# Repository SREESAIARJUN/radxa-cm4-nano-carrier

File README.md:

# Radxa CM4 Nano Carrier Board (Revision 5.0)

# Radxa CM4 Nano Carrier Board, Rev 5.0: Engineering Design Document

**Status:** Preliminary. Several specification conflicts must be resolved before layout (see Section 0).

---

## 0. Design Review Findings (Read First)

These issues were found in the input specification. Each one blocks layout or puts first-pass success at risk.

| # | Severity | Issue | Recommendation |
|---|---|---|---|
| R1 | **Blocker** | **Mounting holes at 2.25 mm inset are too close to the edge.** An M2.5 hole needs a Ø2.7 mm drill and a Ø4.5–5.0 mm keep-out pad for the screw head or standoff. A Ø5.0 mm pad at a 2.25 mm inset extends 0.25 mm past the board edge. A 5 mm A/F hex standoff (corner radius ≈ 2.89 mm) overhangs by up to 0.64 mm. This violates the 0.0 mm overhang rule. | Move holes to a ≥3.0 mm inset (pad fully on-board), or use Ø4.0 mm pads with a low-profile M2.5 head. |
| R2 | **Blocker** | **Hole pattern does not match the module.** The CM4 form factor (which Radxa CM-series modules follow) uses a 48.0 × 32.0 mm hole pitch at a 3.5 mm inset (verify against the Radxa mechanical drawing). The specified 50.5 × 35.5 mm pitch will not align with the module's holes. | Adopt the module hole pattern, at least for the shared holes. |
| R3 | **High** | **Connector spacing is unverified.** I cannot confirm that the 15.0 mm centre-to-centre spacing matches the module. A mismatch prevents the module from seating. | Take the connector X/Y origins directly from the Radxa CM4 mechanical DXF. |
| R4 | **High** | *(row truncated by the Rev 5 edit - the complete Rev 4 findings table is preserved in git commit `7eb46b7`)* | See commit `7eb46b7`. |

---

## Revision 9.0 Engineering Changelog

**Task:** Gigabit Ethernet PHY interface: 100-ohm differential routing for TRD0..TRD3 to an ultra-low-profile vertical RJ45.

**Result:** the full 1000BASE-T MDI chain is placed, routed, and verified. It runs from the CM4 module's on-board PHY (DF40 J1 pins 3-12) through discrete magnetics (T1) to a bottom-side vertical RJ45 (J3). The routing passes 4 x 100-ohm pairs on a field-solved stackup, with intra-pair skew of 0.000 mm and zero DRC violations attributable to Rev 9. `tools/ethernet_mdi.py verify` passes **26/26** checks (`artifacts/rev9_mdi_si_report.md`).

### 9.1 Changes implemented

| File | Change |
|---|---|
| `tools/mdi_impedance.py` (new) | The single source of truth for the stackup and the MDI geometry. It contains two independent impedance models: a 2-D finite-difference Laplace field solver (solder mask, finite copper thickness, discrete Gauss-law charge) and the Hammerstad-Jensen / Kirschning-Jansen closed forms. It also has a self-test, a width solver, and a fab-tolerance corner sweep. Run `--check` to exercise all three. |
| `tools/ethernet_mdi.py` (new) | Generator and verifier for the Rev 9 stage. It writes the footprints, places T1/J3/passives, routes all 16 MDI nets plus the centre-tap, Bob Smith, and shield networks, pours the In1/In2 planes, and writes the netclass and DRU rules. The `verify` command checks SI, polarity, and mechanics, runs DRC with mutation tests, and checks ERC and parity. `render` and `schematic` are also provided. |
| `lib/radxa-cm4-nano-carrier.pretty/` | New footprints: `Pulse_H5007NL_SMD-24_P1.27mm`, `Amphenol_RJE231881317T_RJ45_Vertical_SMD`, `C/R_0402_1005Metric`, `C_1206_3216Metric_HV`, `R_1206_3216Metric`. Land patterns are taken from the manufacturer drawings via the LCSC/EasyEDA pad data. |
| `radxa-cm4-nano-carrier.kicad_pcb` | Adds the JLC04161H-7628 stackup (`setup/stackup`), T1, J3, C10-C15, and R10-R14. It adds 4 PHY-side and 4 cable-side 100-ohm pairs, In1/In2 GND planes with an ETH_SHIELD island and a 2.0 mm hi-pot split, and GND/shield stitching. Every Rev 9 item belongs to group `REV9_ETH_MDI`. |
| `radxa-cm4-nano-carrier.kicad_pro` | Adds netclass `ETH_MDI_100R` (W 0.165 / gap 0.125 / via 0.50/0.30) with patterns `Ethernet_Pair*` and `ETH_MDI*`. The netclasses of other stages are preserved. |
| `radxa-cm4-nano-carrier.kicad_dru` | Adds a Rev 9 rule block for track width, diff-pair gap, uncoupled length, length, and via count. It adds `mdi_isolation` (0.30 mm to every other net's tracks, vias, and planes), `mdi_interpair` (0.30 mm), one skew rule (max 0.15 mm) for each of the 8 pair segments, and `eth_shield_split` (2.0 mm on the inner layers). Each rule is shown to be live by a mutation test. |
| `radxa-cm4-nano-carrier.kicad_sch`, `lib/CM4Carrier.kicad_sym` | Adds T1, J3, and C10-C15 / R10-R14 symbols with global labels whose net names are read back from the board. Schematic-to-PCB parity for the Rev 9 parts is clean. |
| `fp-lib-table` | **Bug fix:** the table is now merged rather than overwritten. It registers `CM4Carrier` (used by the schematic hole symbols), which removes the Rev 7 `lib_footprint_issues` DRC errors. |
| `README.md` | **Bug fix:** closed the findings-table row R4, which an earlier edit had truncated mid-sentence. |

### 9.2 Architecture

**Signal chain:** CM4 PHY (on-module) -> J1 DF40 pins 3-12 -> T1 Pulse H5007NL (1000BASE-T, 1CT:1CT, 1500 Vrms, LCSC C6384935) -> J3 Amphenol RJE231881317T (8P8C vertical SMT, shielded, 13.1 mm, LCSC C5384839).

**Placement:** the whole top side lies under the module and is limited to 1.2 mm part height, so T1, J3, and the 1206 HV parts are on **B.Cu**. On the top side there are only eight 0402s (0.55 mm tall) at the T1 centre and cable taps. T1 sits at (34.0, 20.0) with its PHY row facing east and pin 1 at the top. J3 sits at (11.0, 20.0) with its contacts facing T1, and the plug enters from below the carrier.

**Stackup and geometry** (`mdi_impedance.py`): JLC04161H-7628, L1/L4 microstrip over solid L2/L3 GND, 7628 prepreg 0.2104 mm, er 4.4, 10 um LPI mask. The chosen geometry is **W 0.165 mm / S 0.125 mm**, solved with the field solver to **100.03 ohm** (Zodd 50.0, Zcomm 44.2, 5.52 ps/mm).

| Model | Zdiff (ohm) |
|---|---|
| FD field solver, masked (sign-off) | 100.03 |
| FD field solver, bare copper | 104.71 |
| Kirschning-Jansen closed form, bare | 111.06 (its strip-thickness correction under-predicts the side-wall coupling across a 0.125 mm gap with 35 um copper; with thin copper it agrees with the FD solver to within 1.2-1.9 %) |
| Fab corners, one at a time (etch +/-0.02, prepreg +/-10 %, er +/-0.2) | 91.5 - 108.8 (inside +/-10 %) |
| All corners aligned worst case | 88.4 - 112.3, so order JLC impedance control at +/-10 % |

**Channel map and polarity.** On the bottom side both T1 and J3 are mirrored. Their two pad rows then always meet in *reversed* pair order, whatever the rotation. Two degrees of freedom absorb this without any pair crossing:

| CM4 pair | T1 channel (top -> bottom) | P lands on | Cable net | RJ45 pins (+/-) |
|---|---|---|---|---|
| Pair3 (TRD3) | ch1 | TD1- / MX1- | ETH_MDI3 | 7 / 8 |
| Pair1 (TRD1) | ch2 | TD2- / MX2- | ETH_MDI1 | 3 / 6 |
| Pair2 (TRD2) | ch3 | TD3- / MX3- | ETH_MDI2 | 4 / 5 |
| Pair0 (TRD0) | ch4 | TD4- / MX4- | ETH_MDI0 | 1 / 2 |

The four 1CT:1CT channels are identical, and swapping *both* ends of a winding preserves end-to-end polarity. The verifier proves this from the H5007NL dot convention (`MAP-polarity`) and checks the T568 pin map from the copper (`MAP-t568`).

**PHY-side topology:**
- The four pairs leave the 0.4 mm DF40 field. Pair3 and Pair2 come from the outer row through the inter-row gap. Pair1 and Pair0 come from the inner row on F.Cu.
- They run east as nested **F.Cu** bands over the In1 GND plane, then drop south on **B.Cu** over the In2 GND plane in a 43.4-46.8 mm corridor. This corridor is co-planned with the Rev 11 HDMI J4 and the Rev 13 buck. The pairs then turn west into the T1 pads.
- Bands and drops sit over separate solid planes, so they cross freely. **Every pair changes layer exactly once**, and Pair0 uses a compact two-layer via twist.
- GND stitching vias sit beside every layer transition.

**Cable side:** the pairs run almost straight across a 4.1 mm gap, 7.5-11.6 mm per net. Pair C hops to F.Cu with *both* legs, so via counts stay balanced, and passes over pair B's diagonal leg. That leg is the unavoidable T568 3/6 straddle.

**Planes and isolation:**
- In1/In2 are GND everywhere except an **ETH_SHIELD** island (x 0-33, y 11.8-31.5) under the cable side and the jack.
- A **2.0 mm split** runs under the T1 body. This is the 802.3 1500 Vrms functional isolation, enforced by DRU `eth_shield_split`.
- The J3 shield tabs land on the island. R14 (1 Mohm) in parallel with C15 (1 nF / 2 kV, 1206) ties the island to GND and can be tuned at EMC test.
- No MDI segment crosses the split (`REF-domain`), and every MDI segment has copper directly beneath it (`REF-plane`).

**Centre taps:**
- The module PHYs are voltage-mode. Each TCT gets its own **100 nF to GND** (C10-C13, on top under T1). The taps are never shorted together or tied to a supply.
- The cable side uses **Bob Smith** termination: 4 x 75 ohm (R10-R13) to node ETH_BS, then 1 nF / 2 kV (C14) to ETH_SHIELD.

**Pipeline coexistence:**
- Other revisions edit this same board concurrently. The pipeline order is `cm4_mechanical -> ethernet_mdi -> hdmi_tmds -> buck_3v3`.
- `ethernet_mdi.py generate` is **additive and idempotent**. It replaces only its own `REV9_ETH_MDI` group, its footprints, and the Ethernet-net copper and planes, and leaves other stages' groups untouched.
- DRC violations are attributed to Rev 9 by item UUID.

### 9.3 Validation status

| Check | Result |
|---|---|
| Impedance self-test (FD vs H-J / K-J, 8 cases) | PASS, agreement within -1.1 to -1.9 % |
| Nominal Zdiff / fab corners | 100.03 ohm; 91.5-108.8 ohm |
| T568 map, end-to-end polarity, J1 pinout | PASS |
| Intra-pair skew, 8 segments (track + 1.5512 mm per via, KiCad method) | 0.000 mm on all segments (limit 0.15 mm = 0.83 ps) |
| Length per side | max 42.95 mm (limit 50). J1-to-RJ45 totals: 50.9 / 36.5 / 51.5 / 33.6 mm |
| Uncoupled length per net | 3.8-8.8 mm (limit 10). Uncoupled 0.165 mm lines are about 141.7 ohm differential, and the worst case adds -39.6 dB return loss at 100 MHz (limit -30 dB) |
| Pair-to-pair spacing | min 0.495 mm (rule 0.30) |
| Reference planes | 0 voids under MDI copper; 0 split crossings |
| kicad-cli DRC, Rev 9 items | 0 violations, 0 unrouted |
| DRU mutation tests (width, isolation, inter-pair) | 3/3 caught |
| Schematic ERC / PCB parity (Rev 9 refs) | 0 unexpected / 0 parity items |
| CM4 mechanical base (`cm4_mechanical.py verify`) | 32/32 |

**Reproduce:** run `python3 tools/mdi_impedance.py --check`, then `python3 tools/ethernet_mdi.py generate`, `schematic`, `verify`, and `render`.

### 9.4 Open items and assumptions

- **PHY centre-tap mode:** the board assumes voltage-mode drivers (BCM54210PE on RPi CM4, RTL8211F on Radxa CM3). Confirm the Radxa CM4 (RK3576) PHY against its hardware design guide. If it needs a supply on the centre taps, R/C changes at C10-C13 are enough and no reroute is needed.
- **Link/activity LEDs:** J3 has no LEDs, and `Ethernet_nLED1..3` (J1 pins 15/17/19) are left unconnected. Discrete bottom-side LEDs are deferred to a later revision.
- **"Ultra-low-profile":** 13.1 mm is the minimum for a stocked vertical 8P8C with full plug retention. The jack is on the bottom side, so the enclosure needs 13.1 mm of clearance below the carrier.
- **Schematic:** the J1/J2 module connectors are not yet schematic symbols, so the 8 PHY-side `Ethernet_PairN` global labels are expected ERC "dangling" warnings.
- **DF40 pad field:** inside the 0.4 mm-pitch field, MDI stubs keep the netclass's 0.20 mm clearance to J1 pads. The 0.30 mm `mdi_isolation` rule exempts pads by design.

## Revision 11.0 Engineering Changelog

**Task:** Micro HDMI (Type D) connector with HDMI 2.0 100-ohm TMDS differential pairs, length-matched to within 0.15 mm.
**Result:** all 8 TMDS nets are routed and length-matched to **0.0 µm**, measured from the saved copper (each net is 45.1256 mm pad to pad, plus one 1.551 mm via barrel).
**Verification:** `python3 tools/hdmi_tmds.py verify` passes **26/26** checks. Report: `artifacts/rev11_hdmi_tmds_report.md`.

### Changes implemented
- **New stage `tools/hdmi_tmds.py`** (`generate` / `verify` / `solve`). It is the single source of truth for the HDMI0 TMDS breakout and should be edited instead of the copper. `generate` is idempotent: before loading the board it strips its own previous output at the S-expression level. Python deletion through pcbnew is not used because KiCad 8.0.9's SWIG bindings corrupt the board's item lists after `BOARD.Remove()` on tracks.
  Run order: `cm4_mechanical.py generate` → `ethernet_mdi.py generate` → `hdmi_tmds.py generate`. The earlier stages rebuild the board; this one is additive.
- **J4 = XUNPU HDMI-101S Micro-HDMI Type D** (LCSC C720620, 52k in stock).
  - **Footprint:** `lib/radxa-cm4-nano-carrier.pretty/HDMI_Micro-D_XUNPU_HDMI-101S.kicad_mod`. The land pattern is entered numerically from the LCSC/EasyEDA footprint: 19 pads at 0.2 × 0.84 / 0.2 × 1.0 mm in two staggered 0.4 mm-pitch rows, plus 4 oval THT shell slots (Ø0.7 × 1.7 mm).
  - **Placement:** bottom side at (44.0, 36.0). The mouth is 0.25 mm inside the Y=40 edge (zero overhang), and the shell-pad copper is 0.34 mm from the edge. The courtyard clears the H4 standoff keep-out by 0.25 mm. The THT shell legs (X ≥ 40.15) clear the top-side J2 DF40 body (ends at X 36.3).
  - **Pin map:** 3/5 D2, 6/8 D1, 9/11 D0, 12/14 CLK, 1 HPD, 15 CEC, 17 SCL, 18 SDA, 19 `HDMI0_5V`; GND on 4/7/10/13/16 and the shell.
- **Rev 5 envelope was not buildable.** It put uHDMI at X 34.5–41.5, where the shell legs would land inside J2's top-side body. `board_outline.dxf` (via `cm4_mechanical.py`) now carries the real J4 courtyard instead.
- **Impedance:** W 0.165 mm / S 0.125 mm. Solved with the validated 2-D FD solver in `tools/mdi_impedance.py` for the JLC04161H-7628 stackup: Zdiff 100.03 Ω, eeff,odd 2.742, 5.52 ps/mm. The same geometry is used on L1 (over In1 GND) and L4 (over In2 GND).
- **Routing.** Every pair follows the same topology: J4 → north → top lane → west → column (X 37.30 / 38.16) → south → strip lane → west → J2 outer-row pins 170–190.
  - The rear-row pairs (D2→TX2, D0→TX0) run on B.Cu.
  - The front-row pairs (D1→TX1, CLK) cannot pass between the 0.2 mm-gap rear pads. They change layer through a via pair 0.87 mm in front of J4 and run on F.Cu, inside the gap between J2's two pad rows.
  - Every TMDS net has **exactly one via**, so the via barrel cancels in every comparison. Both outer layers are identical microstrips, so physical length equals electrical length.
  - P/N polarity is preserved end to end with no crossovers. TX2's vias sit outboard of the J2 outer row for this reason.
- **Length matching** (solved, then measured back from the copper):
  - *Inter-pair:* chamfered trombones. TX2 gets 3 × 2.45 mm and TX0 3 × 2.58 mm on B.Cu, interleaved between the two strip lanes. TX1 gets 1 × 3.20 mm on its F.Cu riser. Each is found by bisection on the measured length. CLK is naturally the longest and sets the 45.1256 mm target.
  - *Intra-pair:* each route turns a net four 45° left, so P is always the inner trace. It starts 0.89–1.03 mm short (4·d·tan 22.5° = 0.24 mm per 45° turn at a 0.29 mm pitch). This is cancelled by 5–7 single-sided 45° phase bumps on P (h 0.18–0.22 mm, 0.3 mm flat), placed at ≥ 1.05 mm pitch so no contiguous uncoupled stretch exceeds 1 mm.
- **Return path and grounding:**
  - TMDS uses the existing In1/In2 GND planes. A full GND pour is added only on a bare board.
  - Outboard GND vias are placed on J2 pins 186/180/192, plus a GND via 0.73 mm east of the TX2 transition (tied to pin 162) and a plane-stitch via 0.93 mm from the D1/CLK transitions.
  - J4 pins 4 and 16 bond to the GND shell legs.
- **Rules:**
  - `.kicad_pro` gets an `HDMI_TMDS` net class: 0.165 mm width / 0.125 mm gap, 0.50/0.30 mm vias (the project minimums), with exact-name patterns because KiCad patterns are glob-only.
  - `.kicad_dru` gets a fenced block (only this block is replaced on regeneration; other stages' blocks are kept):
    - `hdmi0_tmds_skew_<pair>` at max 0.075 mm. KiCad 8 measures `skew` against the group average, so a two-net group gives |P−N| ≤ 0.15 mm.
    - `hdmi0_tmds_length_window` at L ± 0.075 mm on all 8 nets, for inter-pair matching.
    - Track width 0.160–0.170 mm.
    - Diff-pair gap ≥ 0.115 mm.
    - 0.20 mm TMDS-to-other clearance.
    - One via per net.

### Architecture improvements
- **Co-designed floor plan.** The concurrent Ethernet stage owns an `ETH_SHIELD` island and its 2 mm hi-pot split (no GND for X < 36.5 and 9.8 < Y < 33.5), plus RJ45 J3, T1, and MDI routing down the east side. Two earlier J4 placements I tried (left edge, right edge) collided with successive versions of that plan. The final placement keeps every TMDS segment inside the solid-GND "L" (X > 36.5, or Y > 34.1). The verifier samples 10,827 points along and ±0.28 mm beside every segment and confirms each one lies over *filled* GND. Any future floor-plan change that puts TMDS over the split will fail loudly.
- **The verifier measures the copper, not the model.** Every check reads lengths, gaps, coupled intervals (chained segment by segment), reference-plane fill, return-via distances, pad connectivity and mechanics from the saved board with pcbnew. kicad-cli then runs DRC on the real rules.
- **Mutation tests are baseline-relative.** Each one must create a *new* violation on TMDS copper: lengthening one N trace by 0.20 mm must raise `skew_out_of_range`, and adding a GND track 0.15 mm from a TMDS trace must raise `clearance`. Pre-existing violations from other stages can't satisfy them.
- **Independent review:** a 3-lens adversarial review with per-finding refutation confirmed six findings. Four are fixed: a DRU-block deletion that would have wiped the Rev 13/Rev 9 rules, the wrong skew-rule semantics, unconnected J4 GND pins, and a missing TX2 return via. Two are recorded as open items below.

### Validation status
| Item | Status |
|---|---|
| All 8 TMDS nets: max − min ≤ 0.15 mm (inter- **and** intra-pair) | **PASS**: 0.0 µm (0.000 ps) |
| Coupled gap 0.125 mm on every coupled run; pair-to-pair ≥ 0.40 mm | **PASS**: 0.1250 mm / 0.400 mm |
| Longest contiguous uncoupled stretch ≤ 1.0 mm (5.5 ps ≪ ~50 ps edge) | **PASS**: 0.85–0.94 mm |
| Every TMDS segment over filled GND (outside the 0.75 mm via-transition zones) | **PASS**: 0 off-plane of 10,827 samples |
| GND return within 2.0 mm of every layer change | **PASS**: 0.73–1.72 mm |
| kicad-cli DRC, violations touching TMDS / J4 | **PASS**: 0 |
| DRU mutation tests (skew, clearance) | **PASS**: both caught |
| Insertion length vs HDMI 2.0 (UI 168 ps at 5.94 Gbit/s) | 45.13 mm = 249 ps; 0.15 mm = 0.83 ps = 0.5 % UI |
| Whole-board DRC | **Not clean (other stages):** 162 items, none touching TMDS/J4 (mostly Ethernet-stage clearance) |

**Open items (Rev 12+):**
1. J4 shield pins **7, 10, 13** are not connected yet. There is no via site under the F.Cu risers or between the J4 via pairs. Fixing this needs via-in-pad, or a re-planned D1/CLK escape.
2. **TPD4E05U06 ESD** (required by `specs/carrier_specs.md`) is not placed. It will need flow-through placement next to J4 and a re-solve of the length matching through its pads.
3. **`HDMI0_5V`** (pin 19) has no source yet. It needs a current-limited, back-drive-protected 5 V feed.
4. HPD, CEC and DDC are not routed yet.
5. J4 is not in the schematic yet, so schematic/PCB parity is open.
6. The connector mouth/body outline is approximate. Confirm it against the XUNPU mechanical drawing before release.

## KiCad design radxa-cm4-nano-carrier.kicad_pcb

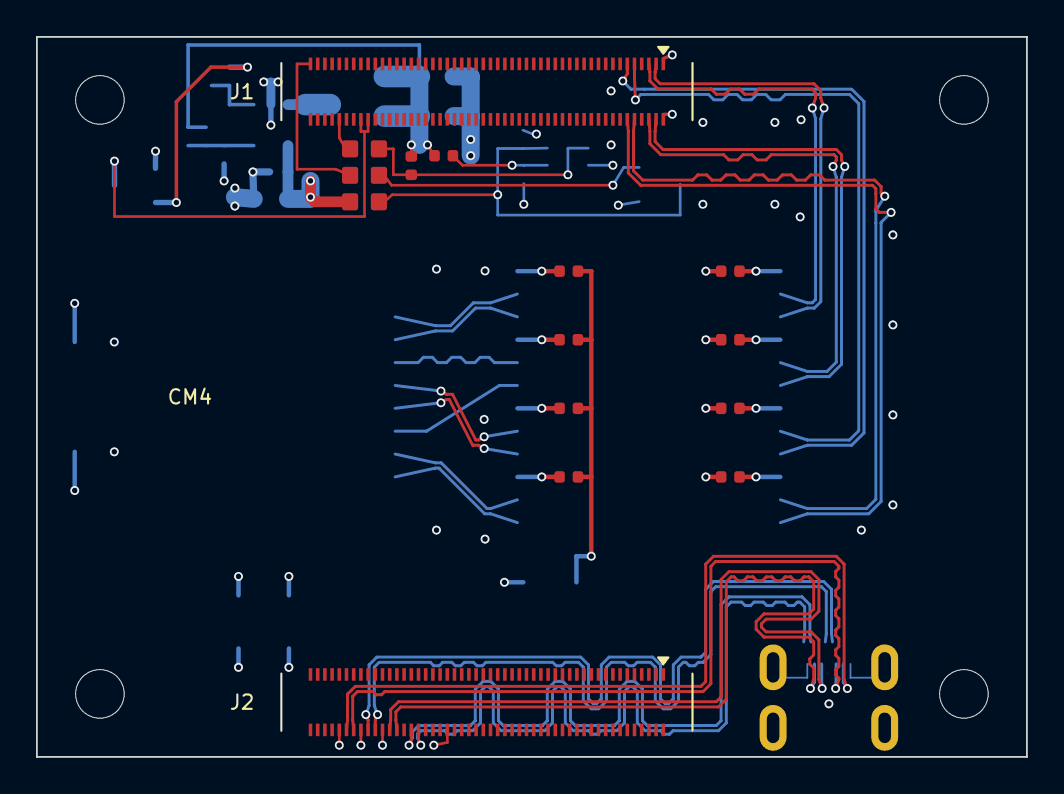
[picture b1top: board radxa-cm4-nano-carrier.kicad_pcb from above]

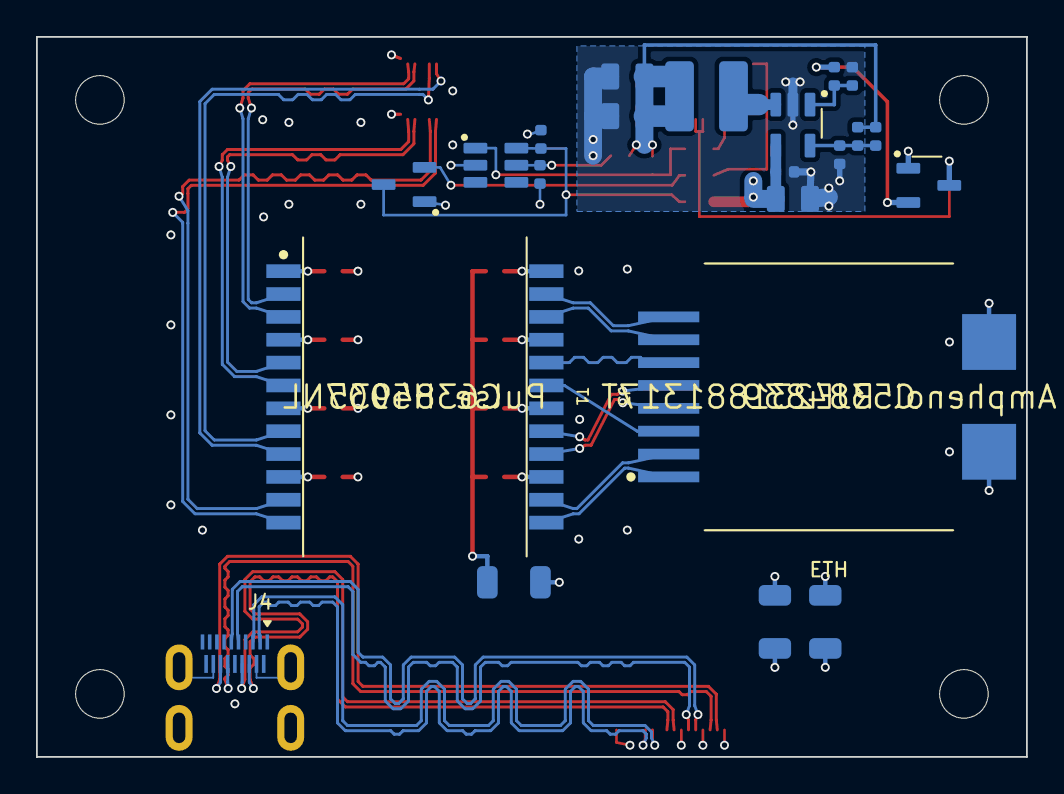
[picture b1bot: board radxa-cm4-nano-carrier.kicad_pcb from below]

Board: 4 copper layers, 55.0 x 40.0 mm, 41 parts (22 on the bottom side), 53 nets.

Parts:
C10, C11, C12, C13, C41, C50: 100nF 16V X7R; C_0402_1005Metric
C14, C15: 1nF 2kV X7R; C_1206_3216Metric_HV
C40, C42, C43: 22uF 25V X5R; C_0805_2012Metric
C44: 47pF 50V C0G; C_0402_1005Metric
H1, H2, H3, H4: M2.5 x 3.0 mm standoff; MountingHole_2.7mm_M2.5_CM4
J1, J2: DF40HC(3.0)-100DS-0.4V(51); Hirose_DF40HC-3.0-100DS-0.4V_2x50_P0.4mm
J3: RJE231881317T; Amphenol_RJE231881317T_RJ45_Vertical_SMD
J4: HDMI-101S; HDMI_Micro-D_XUNPU_HDMI-101S
L1: 2.2uH 5.8A 39mR; L_4.0x4.0mm_cjiang_FNR4030
R10, R11, R12, R13: 75R 1%; R_0402_1005Metric
R14: 1M 1206; R_1206_3216Metric
R40: 100k 0.1% 25ppm; R_0402_1005Metric
R41: 22.1k 0.1% 25ppm; R_0402_1005Metric
R42, R53: 10k 1%; R_0402_1005Metric
R43: 1M 1%; R_0402_1005Metric
R51: 100k 1% (RADXA only); R_0402_1005Metric
R52: 61.9k 1%; R_0402_1005Metric
R54: 0R 0603 (RPI_CM4 only); R_0603_1608Metric_Bridge
R55: 220R 1% 0603 (RPI_CM4 only); R_0603_1608Metric_Bridge
R56: 10R 1% 0603; R_0603_1608Metric_Bridge
T1: H5007NL; Pulse_H5007NL_SMD-24_P1.27mm
U5: SY8089AAAC; SOT-23-5_Silergy_SY8089
U6: MAX809STRG 2.93V; SOT-23_onsemi_MAX809
U7: MIC803-44D3VM3-TR (RPI_CM4 only); SOT-23_Microchip_MIC803
U8: TPS3808G01DBVR; SOT-23-6_TI_DBV_TPS3808

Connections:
+1V8_OUT: J1.88, J1.90
+3V3_OUT: J1.84, J1.86, U6.3
+3V3_SYS: C42.1, C43.1, C44.2, L1.2, R40.2, R51.1, R52.1
+5V_IN: C40.1, C41.1, J1.77, J1.79, J1.81, J1.83, J1.85, J1.87, R56.1, U5.4
BUCK_EN: R42.1, R43.1, U5.1
BUCK_EN_SRC: R42.2, U6.2
BUCK_FB: C44.1, R40.1, R41.1, U5.5
BUCK_LX: L1.1, U5.3
ETH_BS: C14.2, R10.2, R11.2, R12.2, R13.2
ETH_MCT1: R10.1, T1.24
ETH_MCT2: R11.1, T1.21
ETH_MCT3: R12.1, T1.18
ETH_MCT4: R13.1, T1.15
ETH_MDI0_N: J3.2, T1.14
ETH_MDI0_P: J3.1, T1.13
ETH_MDI1_N: J3.6, T1.20
ETH_MDI1_P: J3.3, T1.19
ETH_MDI2_N: J3.5, T1.17
ETH_MDI2_P: J3.4, T1.16
ETH_MDI3_N: J3.8, T1.23
ETH_MDI3_P: J3.7, T1.22
ETH_SHIELD: C14.1, C15.2, J3.M1, J3.M2, R14.2
ETH_TCT1: C10.2, T1.1
ETH_TCT2: C11.2, T1.4
ETH_TCT3: C12.2, T1.7
ETH_TCT4: C13.2, T1.10
Ethernet_Pair0_N: J1.10, T1.11
Ethernet_Pair0_P: J1.12, T1.12
Ethernet_Pair1_N: J1.6, T1.5
Ethernet_Pair1_P: J1.4, T1.6
Ethernet_Pair2_N: J1.9, T1.8
Ethernet_Pair2_P: J1.11, T1.9
Ethernet_Pair3_N: J1.5, T1.2
Ethernet_Pair3_P: J1.3, T1.3
GLOBAL_EN: J1.99, R54.1
GND: C10.1, C11.1, C12.1, C13.1, C15.1, C40.2, C41.2, C42.2, C43.2, C50.2, J1.1, J1.2, J1.7, J1.8, J1.13, J1.14, J1.22, J1.23, J1.32, J1.33, J1.42, J1.43, J1.52, J1.53, J1.59, J1.60, J1.65, J1.66, J1.71, J1.74, J1.98, J2.7, J2.8, J2.13, J2.14, J2.19, J2.20, J2.25, J2.26, J2.31, J2.32, J2.37, J2.38, J2.44, J2.50, J2.55, J2.56, J2.61, J2.62, J2.67, J2.68, J2.73, J2.74, J2.79, J2.80, J2.85, J2.86, J2.91, J2.92, J2.97, J2.98, J4.4, J4.7, J4.10, J4.13, J4.16, J4.20, R14.1, R41.2, R43.2, R53.2, U5.2, U6.1, U7.1, U8.2
HDMI0_CEC: J2.51, J4.15
HDMI0_CLK_N: J2.90, J4.14
HDMI0_CLK_P: J2.88, J4.12
HDMI0_HOTPLUG: J2.53, J4.1
HDMI0_SCL: J2.100, J4.17
HDMI0_SDA: J2.99, J4.18
HDMI0_TX0_N: J2.84, J4.11
HDMI0_TX0_P: J2.82, J4.9
HDMI0_TX1_N: J2.78, J4.8
HDMI0_TX1_P: J2.76, J4.6
HDMI0_TX2_N: J2.72, J4.5
HDMI0_TX2_P: J2.70, J4.3
PSEQ_PWR_OK: R51.2, R55.2, U8.1
PSEQ_SENSE_3V3: R52.2, R53.1, U8.5
PSEQ_VDD: C50.1, R56.2, U7.3, U8.6
PSEQ_VIN_OK: R54.2, U7.2
RUN_PG: J1.92, R55.1

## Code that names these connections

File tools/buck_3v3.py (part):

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    "C43": (FP_C0805, "22uF 25V X5R", "C45783", "CL21A226MAQNNNE", (52.70, 20.25), "+3V3_SYS", (52.70, 22.15), "GND"),
    # Feedback: R40 top (sense -> FB), R41 bottom (FB -> GND), C44 feed-forward across R40
    "R41": (FP_R0402, "22.1k 0.1% 25ppm", "C2692911", "PTFR0402B22K1P9",
            (U_PIN["5"][0], 9.40), "BUCK_FB", (U_PIN["5"][0] - 2 * R04, 9.40), "GND"),
    "R40": (FP_R0402, "100k 0.1% 25ppm", "C852472", "RT0402BRD07100KL",
            (U_PIN["5"][0], 8.40), "BUCK_FB", (U_PIN["5"][0] + 2 * R04, 8.40), "+3V3_SYS"),
    "C44": (FP_C0402, "47pF 50V C0G", "C1567", "CL05C470JB5NNNC",
            (U_PIN["5"][0], 7.40), "BUCK_FB", (U_PIN["5"][0] + 2 * R04, 7.40), "+3V3_SYS"),
    # EN: R42 series from module +3V3_OUT, R43 1M pull-down
    "R42": (FP_R0402, "10k 1%", "C25744", "0402WGF1002TCE", (52.20, 9.70), "BUCK_EN", (53.22, 9.70), "BUCK_EN_SRC"),
    "R43": (FP_R0402, "1M 1%", "C26083", "0402WGF1004TCE", (52.20, 8.70), "BUCK_EN", (53.22, 8.70), "GND"),
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# board-frame extras: (pts, net, width, layer)
U6_TRACKS = [
    ([U6_PIN["1"], U6_VIA_GND], "GND", 0.30, "B.Cu"),
    ([U6_PIN["2"], U6_VIA_OUT], "BUCK_EN_SRC", 0.30, "B.Cu"),
    ([U6_PIN["3"], U6_VIA_VCC], "+3V3_OUT", 0.30, "B.Cu"),
    # F.Cu jumper over the Kelvin-sense loop (which encloses U5 EN on B.Cu) to the R42 landing via
    ([U6_VIA_OUT, (7.75, 3.60), (9.67, 1.68), xf((53.22, 10.70))], "BUCK_EN_SRC", 0.20, "F.Cu"),
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    T.append(([(45.50, 10.00), (46.50, 10.00)], "GND", 0.40))
    T.append(([c["R41"][1], (46.90, 9.40)], "GND", 0.30))
    # LX: pin 3 straight south into L1 pad 1 (0.6 at the pin, 1.2 once clear of pin 2)
    T.append(([p["3"], (p["3"][0], 13.90)], "BUCK_LX", W_PIN))
    T.append(([(p["3"][0], 13.90), (p["3"][0], 15.30)], "BUCK_LX", W_LX))
    # VOUT: L1 pad 2 -> C42 / C43, C42 <-> C43, C42 -> distribution vias
    T.append(([(50.50, 18.30), c["C42"][0]], "+3V3_SYS", W_LX))
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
